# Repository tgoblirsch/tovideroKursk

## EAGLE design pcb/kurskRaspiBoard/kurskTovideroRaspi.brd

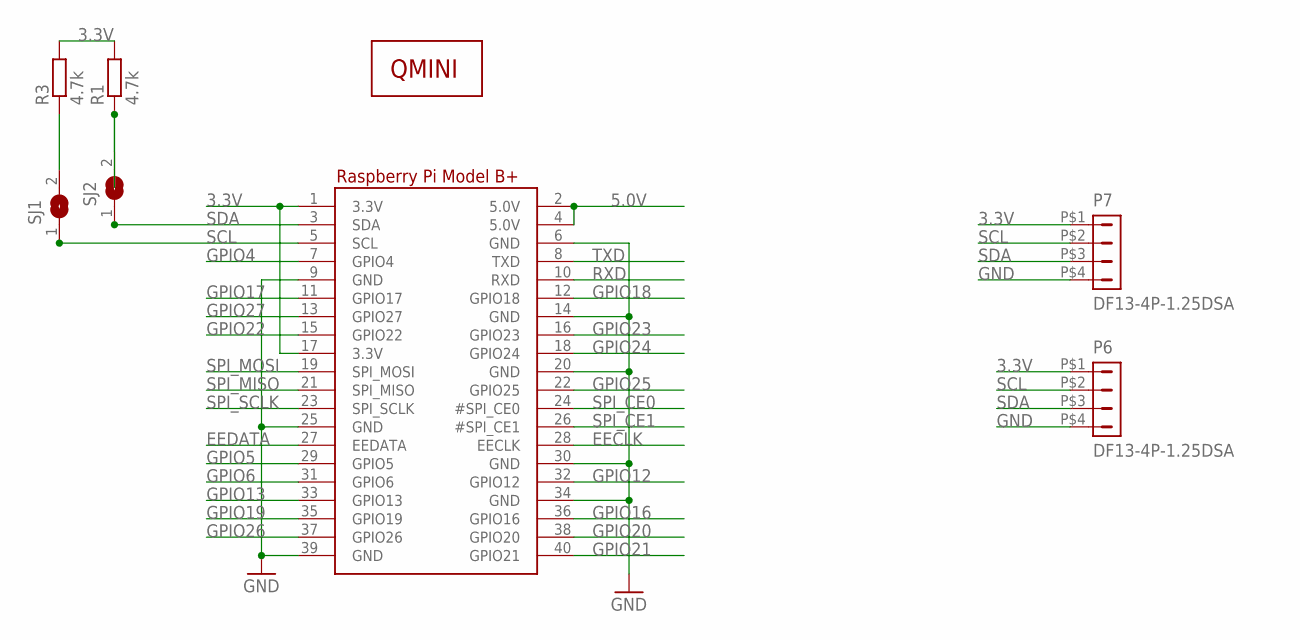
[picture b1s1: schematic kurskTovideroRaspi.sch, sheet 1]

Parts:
P6: DF13-4P-1.25DSA; MANUFACTURERPARTNUMBER UNKNOWN MANUFACTURER PART NUMBER; DIGIKEY H2193-ND
P7: DF13-4P-1.25DSA; MANUFACTURERPARTNUMBER UNKNOWN MANUFACTURER PART NUMBER; DIGIKEY# H2193-ND
R1, R3: 4.7k; R0805; MANUFACTURERPARTNUMBER UNKNOWN MANUFACTURER PART NUMBER; DIGIKEY 541-4.70KCCT-ND
RPI1: RASPBERRYPI_BPLUS_HATNOSLOTS; PI_HAT_NOSLOTS; MANUFACTURERPARTNUMBER UNKNOWN MANUFACTURER PART NUMBER
SJ1, SJ2: SJ
U$1: QMINI; MANUFACTURERPARTNUMBER UNKNOWN MANUFACTURER PART NUMBER

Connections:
3.3V: P6.P$1 (1), P7.P$1 (1), R1.2, R3.2, RPI1.1 (3.3V), RPI1.17 (3.3V); also elsewhere on the board
5.0V: RPI1.2 (5.0V), RPI1.4 (5.0V); also elsewhere on the board
EECLK: RPI1.28 (EECLK)
EEDATA: RPI1.27 (EEDATA)
GND: P6.P$4 (4), P7.P$4 (4), RPI1.6 (GND), RPI1.9 (GND), RPI1.14 (GND), RPI1.20 (GND), RPI1.25 (GND), RPI1.30 (GND), RPI1.34 (GND), RPI1.39 (GND); also elsewhere on the board
GPIO4: RPI1.7 (GPIO4)
GPIO5: RPI1.29 (GPIO5)
GPIO6: RPI1.31 (GPIO6)
GPIO12: RPI1.32 (GPIO12)
GPIO13: RPI1.33 (GPIO13)
GPIO16: RPI1.36 (GPIO16)
GPIO17: RPI1.11 (GPIO17); also elsewhere on the board
GPIO18: RPI1.12 (GPIO18)
GPIO19: RPI1.35 (GPIO19)
GPIO20: RPI1.38 (GPIO20)
GPIO21: RPI1.40 (GPIO21)
GPIO22: RPI1.15 (GPIO22); also elsewhere on the board
GPIO23: RPI1.16 (GPIO23)
GPIO24: RPI1.18 (GPIO24)
GPIO25: RPI1.22 (GPIO25)
GPIO26: RPI1.37 (GPIO26)
GPIO27: RPI1.13 (GPIO27); also elsewhere on the board
unnamed: R3.1, SJ1.2
unnamed: R1.1, SJ2.2
RXD: RPI1.10 (RXD)
SCL: P6.P$2 (2), P7.P$2 (2), RPI1.5 (SCL), SJ1.1; also elsewhere on the board
SDA: P6.P$3 (3), P7.P$3 (3), RPI1.3 (SDA), SJ2.1; also elsewhere on the board
SPI_CE0: RPI1.24 (#SPI_CE0)
SPI_CE1: RPI1.26 (#SPI_CE1)
SPI_MISO: RPI1.21 (SPI_MISO)
SPI_MOSI: RPI1.19 (SPI_MOSI)
SPI_SCLK: RPI1.23 (SPI_SCLK)
TXD: RPI1.8 (TXD)

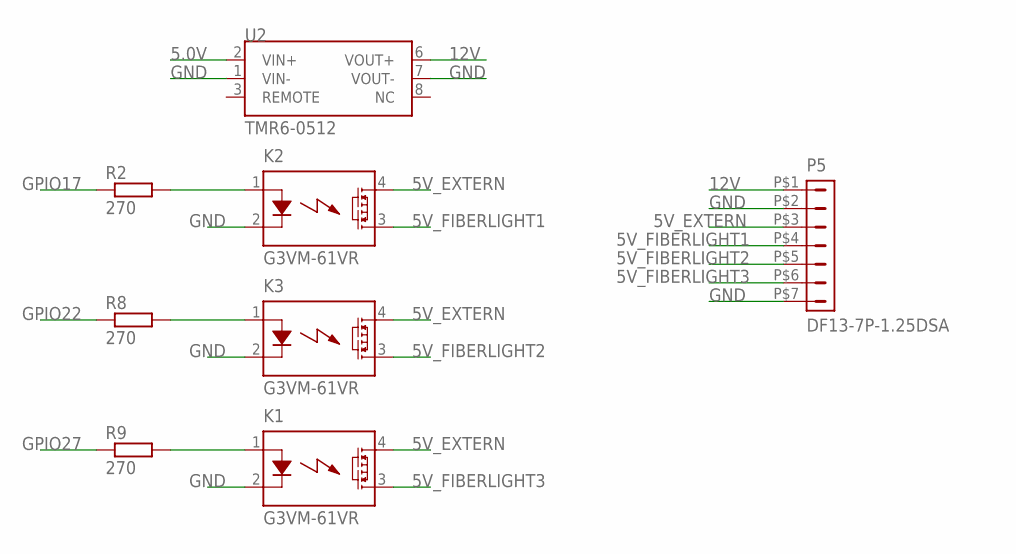
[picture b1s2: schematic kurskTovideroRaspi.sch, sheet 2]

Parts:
K1, K2, K3: G3VM-61VR; SOP04; MANUFACTURERPARTNUMBER UNKNOWN MANUFACTURER PART NUMBER; DIGIKEY Z10319CT-ND
P5: DF13-7P-1.25DSA; MANUFACTURERPARTNUMBER UNKNOWN MANUFACTURER PART NUMBER; DIGIKEY H2196-ND
R2, R8, R9: 270; R0805; MANUFACTURERPARTNUMBER UNKNOWN MANUFACTURER PART NUMBER; DIGIKEY P270CCT-ND
U2: TMR6-0512; MANUFACTURERPARTNUMBER UNKNOWN MANUFACTURER PART NUMBER; DIGIKEY 1951-2391-ND

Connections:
5.0V: U2.2 (VIN+); also elsewhere on the board
5V_EXTERN: K1.4 (DS1), K2.4 (DS1), K3.4 (DS1), P5.P$3 (3)
5V_FIBERLIGHT1: K2.3 (DS2), P5.P$4 (4)
5V_FIBERLIGHT2: K3.3 (DS2), P5.P$5 (5)
5V_FIBERLIGHT3: K1.3 (DS2), P5.P$6 (6)
12V: P5.P$1 (1), U2.6 (VOUT+)
GND: K1.2 (K), K2.2 (K), K3.2 (K), P5.P$2 (2), P5.P$7 (7), U2.1 (VIN-), U2.7 (VOUT-); also elsewhere on the board
GPIO17: R2.1; also elsewhere on the board
GPIO22: R8.1; also elsewhere on the board
GPIO27: R9.1; also elsewhere on the board
unnamed: K1.1 (A), R9.2
unnamed: K2.1 (A), R2.2
unnamed: K3.1 (A), R8.2

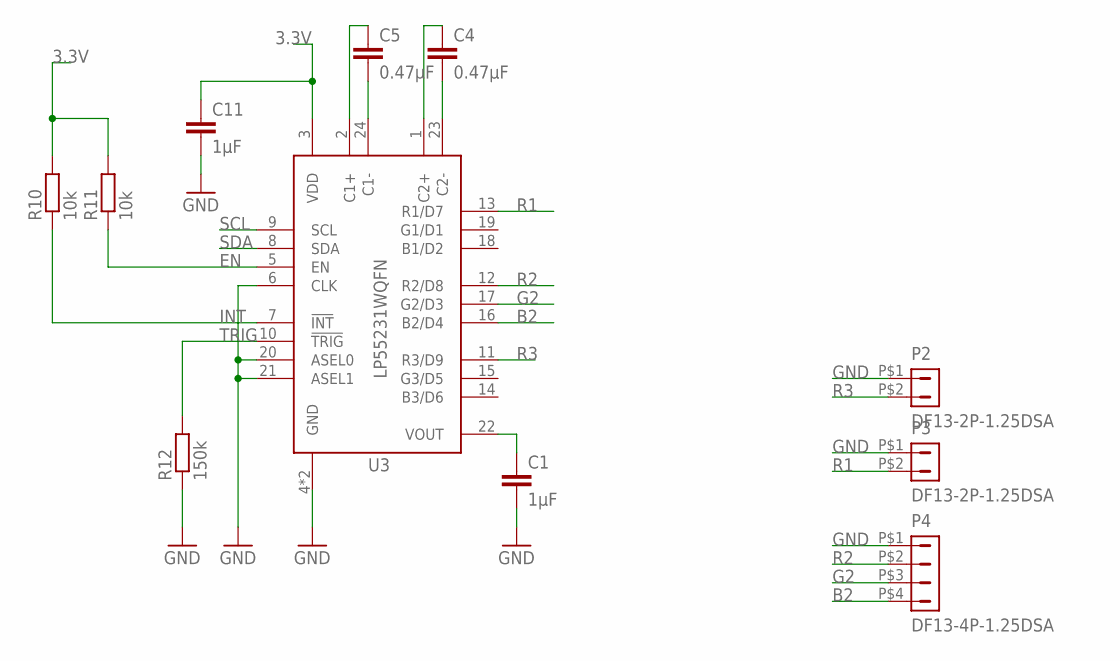
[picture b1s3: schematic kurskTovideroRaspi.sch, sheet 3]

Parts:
C1, C11: 1µF; C0805; MANUFACTURERPARTNUMBER UNKNOWN MANUFACTURER PART NUMBER; DIGIKEY 311-1458-1-ND
C4, C5: 0.47µF; C0805; MANUFACTURERPARTNUMBER UNKNOWN MANUFACTURER PART NUMBER; DIGIKEY 399-9247-1-ND
P2, P3: DF13-2P-1.25DSA; MANUFACTURERPARTNUMBER UNKNOWN MANUFACTURER PART NUMBER; DIGIKEY H2191-ND
P4: DF13-4P-1.25DSA; MANUFACTURERPARTNUMBER UNKNOWN MANUFACTURER PART NUMBER; DIGIKEY H2193-ND
R10, R11: 10k; R0805; MANUFACTURERPARTNUMBER UNKNOWN MANUFACTURER PART NUMBER; DIGIKEY 311-10.0KCRCT-ND
R12: 150k; R0805; MANUFACTURERPARTNUMBER UNKNOWN MANUFACTURER PART NUMBER; DIGIKEY P150KCCT-ND
U3: LP55231WQFN; WQFN-24; MANUFACTURERPARTNUMBER UNKNOWN MANUFACTURER PART NUMBER; DIGIKEY 296-40354-1-ND

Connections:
3.3V: C11.1, R10.2, R11.2, U3.3 (VDD); also elsewhere on the board
B2: P4.P$4 (4), U3.16 (B2/D4)
EN: R11.1, U3.5 (EN)
G2: P4.P$3 (3), U3.17 (G2/D3)
GND: C1.2, C11.2, P2.P$1 (1), P3.P$1 (1), P4.P$1 (1), R12.1, U3.4 (GND), U3.6 (CLK), U3.20 (ASEL0), U3.21 (ASEL1), U3.EP (GND); also elsewhere on the board
INT: R10.1, U3.7 (!INT)
unnamed: C5.2, U3.24 (C1-)
unnamed: C4.2, U3.23 (C2-)
unnamed: C4.1, U3.1 (C2+)
unnamed: C5.1, U3.2 (C1+)
R1: P3.P$2 (2), U3.13 (R1/D7)
R2: P4.P$2 (2), U3.12 (R2/D8)
R3: P2.P$2 (2), U3.11 (R3/D9)
SCL: U3.9 (SCL); also elsewhere on the board
SDA: U3.8 (SDA); also elsewhere on the board
TRIG: R12.2, U3.10 (!TRIG)
VOUT: C1.1, U3.22 (VOUT)

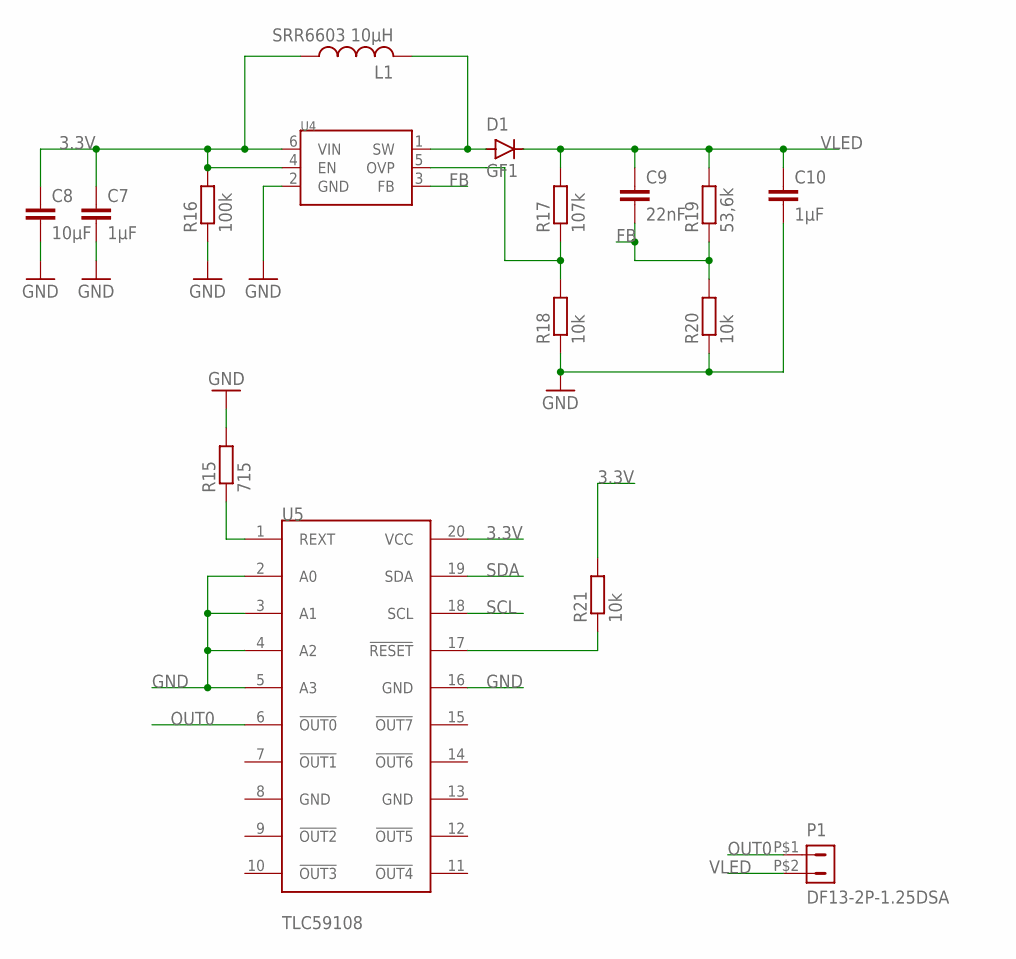
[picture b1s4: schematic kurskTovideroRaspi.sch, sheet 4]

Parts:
C7, C10: 1µF; C0805; MANUFACTURERPARTNUMBER UNKNOWN MANUFACTURER PART NUMBER; DIGIKEY 311-1458-1-ND
C8: 10µF; C0805; MANUFACTURERPARTNUMBER UNKNOWN MANUFACTURER PART NUMBER; DIGIKEY 399-4925-1-ND
C9: 22nF; C0805; MANUFACTURERPARTNUMBER UNKNOWN MANUFACTURER PART NUMBER; DIGIKEY 732-8023-1-ND
D1: GF1; SMA-DO214AC; MANUFACTURERPARTNUMBER UNKNOWN MANUFACTURER PART NUMBER; DIGIKEY EGF1D-E3/67AGICT-ND
L1: SRR6603 10µH; SRR6603; MANUFACTURERPARTNUMBER UNKNOWN MANUFACTURER PART NUMBER; DIGIKEY SRR6603-100MLCT-ND
P1: DF13-2P-1.25DSA; MANUFACTURERPARTNUMBER UNKNOWN MANUFACTURER PART NUMBER; DIGIKEY H2191-ND
R15: 715; R0805; MANUFACTURERPARTNUMBER UNKNOWN MANUFACTURER PART NUMBER; DIGIKEY RMCF0805FT715RCT-ND
R16: 100k; R0805; MANUFACTURERPARTNUMBER UNKNOWN MANUFACTURER PART NUMBER; DIGIKEY 311-100KCRCT-ND
R17: 107k; R0805; MANUFACTURERPARTNUMBER UNKNOWN MANUFACTURER PART NUMBER; DIGIKEY 541-107KCCT-ND
R18, R20, R21: 10k; R0805; MANUFACTURERPARTNUMBER UNKNOWN MANUFACTURER PART NUMBER; DIGIKEY 311-10.0KCRCT-ND
R19: 53,6k; R0805; MANUFACTURERPARTNUMBER UNKNOWN MANUFACTURER PART NUMBER; DIGIKEY P53.6KFCT-ND
U4: MIC2619; SOT-23-6; MANUFACTURERPARTNUMBER UNKNOWN MANUFACTURER PART NUMBER; DIGIKEY 576-3655-1-ND
U5: TLC59108; TSSOP20; MANUFACTURERPARTNUMBER UNKNOWN MANUFACTURER PART NUMBER; DIGIKEY 296-25340-1-ND

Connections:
3.3V: C7.1, C8.1, L1.1, R16.2, R21.2, U4.4 (EN), U4.6 (VIN), U5.20 (VCC); also elsewhere on the board
FB: C9.2, R19.1, R20.2, U4.3 (FB)
GND: C7.2, C8.2, C10.2, R15.2, R16.1, R18.1, R20.1, U4.2 (GND), U5.2 (A0), U5.3 (A1), U5.4 (A2), U5.5 (A3), U5.16 (GND); also elsewhere on the board
unnamed: R15.1, U5.1 (REXT)
unnamed: D1.A, L1.2, U4.1 (SW)
unnamed: R17.1, R18.2, U4.5 (OVP)
unnamed: R21.1, U5.17 (!RESET)
OUT0: P1.P$1 (1), U5.6 (!OUT0)
SCL: U5.18 (SCL); also elsewhere on the board
SDA: U5.19 (SDA); also elsewhere on the board
VLED: C9.1, C10.1, D1.K (C), P1.P$2 (2), R17.2, R19.2

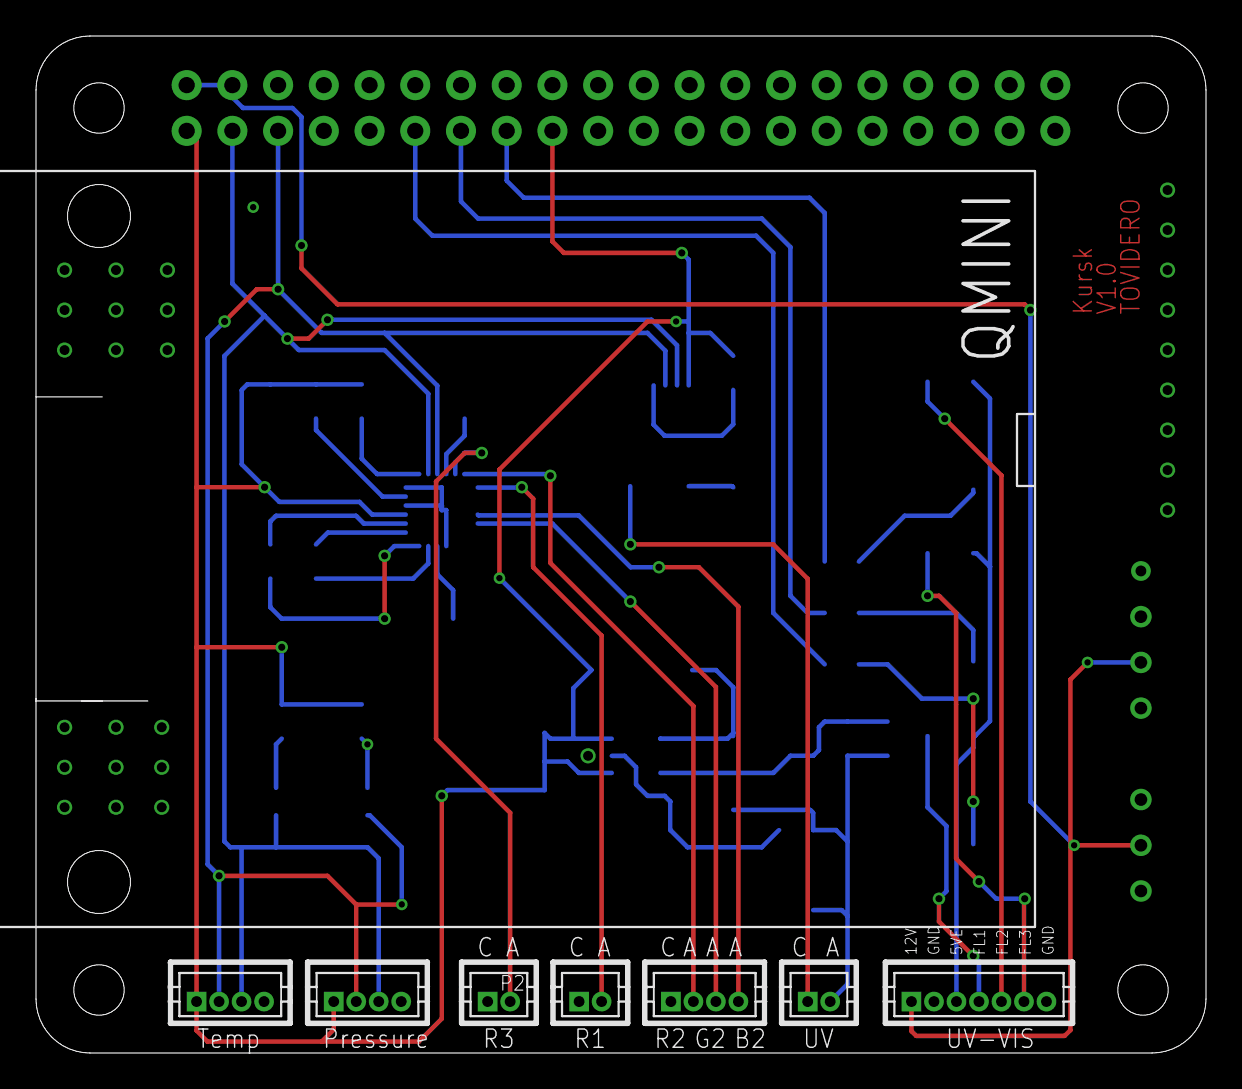
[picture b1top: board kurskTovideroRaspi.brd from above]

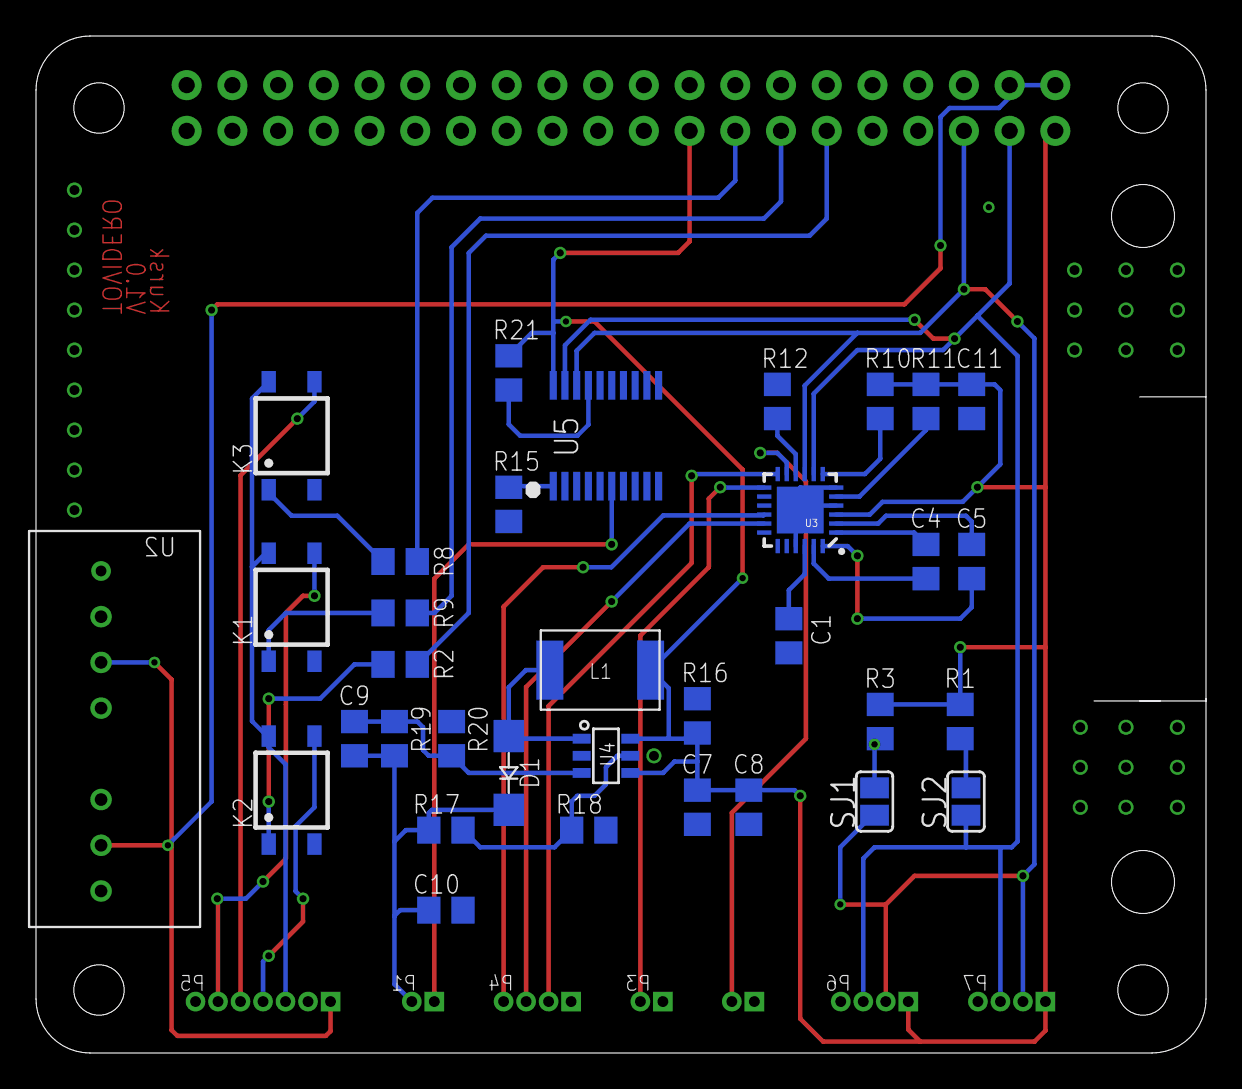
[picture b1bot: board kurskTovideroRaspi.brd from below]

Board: 2 copper layers, 65.0 x 56.5 mm, 43 parts (34 on the bottom side), 38 nets.

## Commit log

2020-03-31 add schematic and board file
2021-11-15 add LED controller to board. new pinout for sensors.

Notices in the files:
parts and their libraries:
microbuilder: This work is placed in the public domain, and may be freely used for commercial and non-commercial work with the following conditions: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
SparkFun-Aesthetics: Licensing: Creative Commons ShareAlike 4.0 International - https://creativecommons.org/licenses/by-sa/4.0
